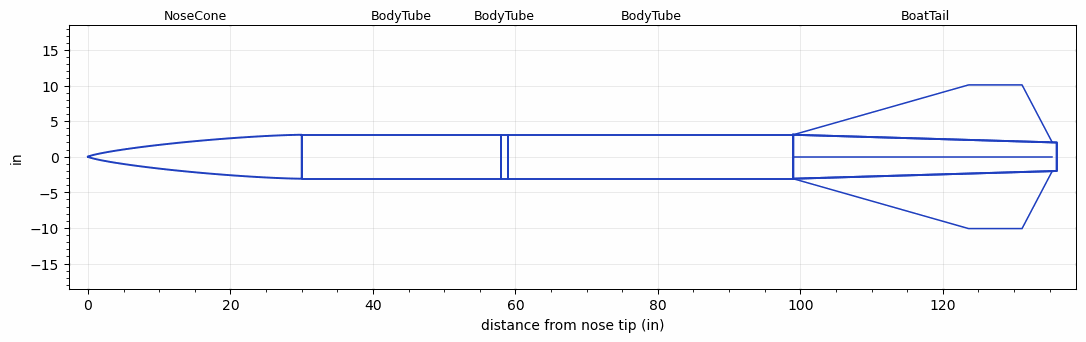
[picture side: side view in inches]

<RASAeroDocument>
 <FileVersion>2</FileVersion>
 <RocketDesign>
  <NoseCone>
   <Length>29.9999</Length>
   <Diameter>6.17</Diameter>
   <Shape>Von Karman Ogive</Shape>
   <Location>0</Location>
  </NoseCone>
  <BodyTube>
   <Length>27.9999</Length>
   <Diameter>6.17</Diameter>
   <Location>29.9999</Location>
  </BodyTube>
  <BodyTube>
   <Length>1</Length>
   <Diameter>6.17</Diameter>
   <Location>57.9998</Location>
  </BodyTube>
  <BodyTube>
   <Length>39.9999</Length>
   <Diameter>6.17</Diameter>
   <RailGuideDiameter>0.63</RailGuideDiameter>
   <RailGuideHeight>0.44</RailGuideHeight>
   <Location>58.9998</Location>
   <BoattailLength>36.9999</BoattailLength>
   <BoattailRearDiameter>4</BoattailRearDiameter>
  </BodyTube>
  <BoatTail>
   <Length>36.9999</Length>
   <Diameter>6.17</Diameter>
   <RearDiameter>4</RearDiameter>
   <Location>98.9997</Location>
   <Fin>
    <Count>4</Count>
    <Chord>36.3616</Chord>
    <Span>7</Span>
    <SweepDistance>24.6221</SweepDistance>
    <TipChord>7.5</TipChord>
    <Thickness>0.25</Thickness>
    <Location>36.9998</Location>
    <AirfoilSection>Rounded</AirfoilSection>
   </Fin>
  </BoatTail>
  <Surface>Smooth Paint</Surface>
  <ModifiedBarrowman>False</ModifiedBarrowman>
  <Turbulence>False</Turbulence>
  <UseBooster1>False</UseBooster1>
  <UseBooster2>False</UseBooster2>
 </RocketDesign>
 <LaunchSite>
  <Altitude>4595</Altitude>
  <Pressure>30.09</Pressure>
  <RodAngle>0</RodAngle>
  <RodLength>17</RodLength>
  <Temperature>100</Temperature>
  <WindSpeed>4.47</WindSpeed>
 </LaunchSite>
 <Recovery>
  <Altitude1>656.168</Altitude1>
  <Altitude2>1000</Altitude2>
  <DeviceType1>Parachute</DeviceType1>
  <DeviceType2>Parachute</DeviceType2>
  <Event1>True</Event1>
  <Event2>True</Event2>
  <Size1>47.9999</Size1>
  <Size2>143.9997</Size2>
  <EventType1>Apogee</EventType1>
  <EventType2>Altitude</EventType2>
  <CD1>2.2</CD1>
  <CD2>2.2</CD2>
 </Recovery>
 <SimulationList>
  <Simulation>
   <SustainerEngine>O5500X  (AT)</SustainerEngine>
   <SustainerLaunchWt>81.8</SustainerLaunchWt>
   <SustainerNozzleDiameter>3.5</SustainerNozzleDiameter>
   <SustainerCG>89.45</SustainerCG>
   <SustainerIgnitionDelay>0</SustainerIgnitionDelay>
   <Booster1SeparationDelay>0</Booster1SeparationDelay>
   <Booster1IgnitionDelay>0</Booster1IgnitionDelay>
   <IncludeBooster1>False</IncludeBooster1>
   <Booster2Delay>0</Booster2Delay>
   <IncludeBooster2>False</IncludeBooster2>
   <TimetoApogee>38.36957</TimetoApogee>
   <MaxAltitude>27862.06</MaxAltitude>
   <MaxVelocity>1881.619</MaxVelocity>
  </Simulation>
  <Simulation>
   <SustainerLaunchWt>78.8792</SustainerLaunchWt>
   <SustainerCG>91.2029</SustainerCG>
   <SustainerIgnitionDelay>0</SustainerIgnitionDelay>
   <Booster1SeparationDelay>0</Booster1SeparationDelay>
   <Booster1IgnitionDelay>0</Booster1IgnitionDelay>
   <IncludeBooster1>False</IncludeBooster1>
   <Booster2Delay>0</Booster2Delay>
   <IncludeBooster2>False</IncludeBooster2>
  </Simulation>
 </SimulationList>
</RASAeroDocument>
